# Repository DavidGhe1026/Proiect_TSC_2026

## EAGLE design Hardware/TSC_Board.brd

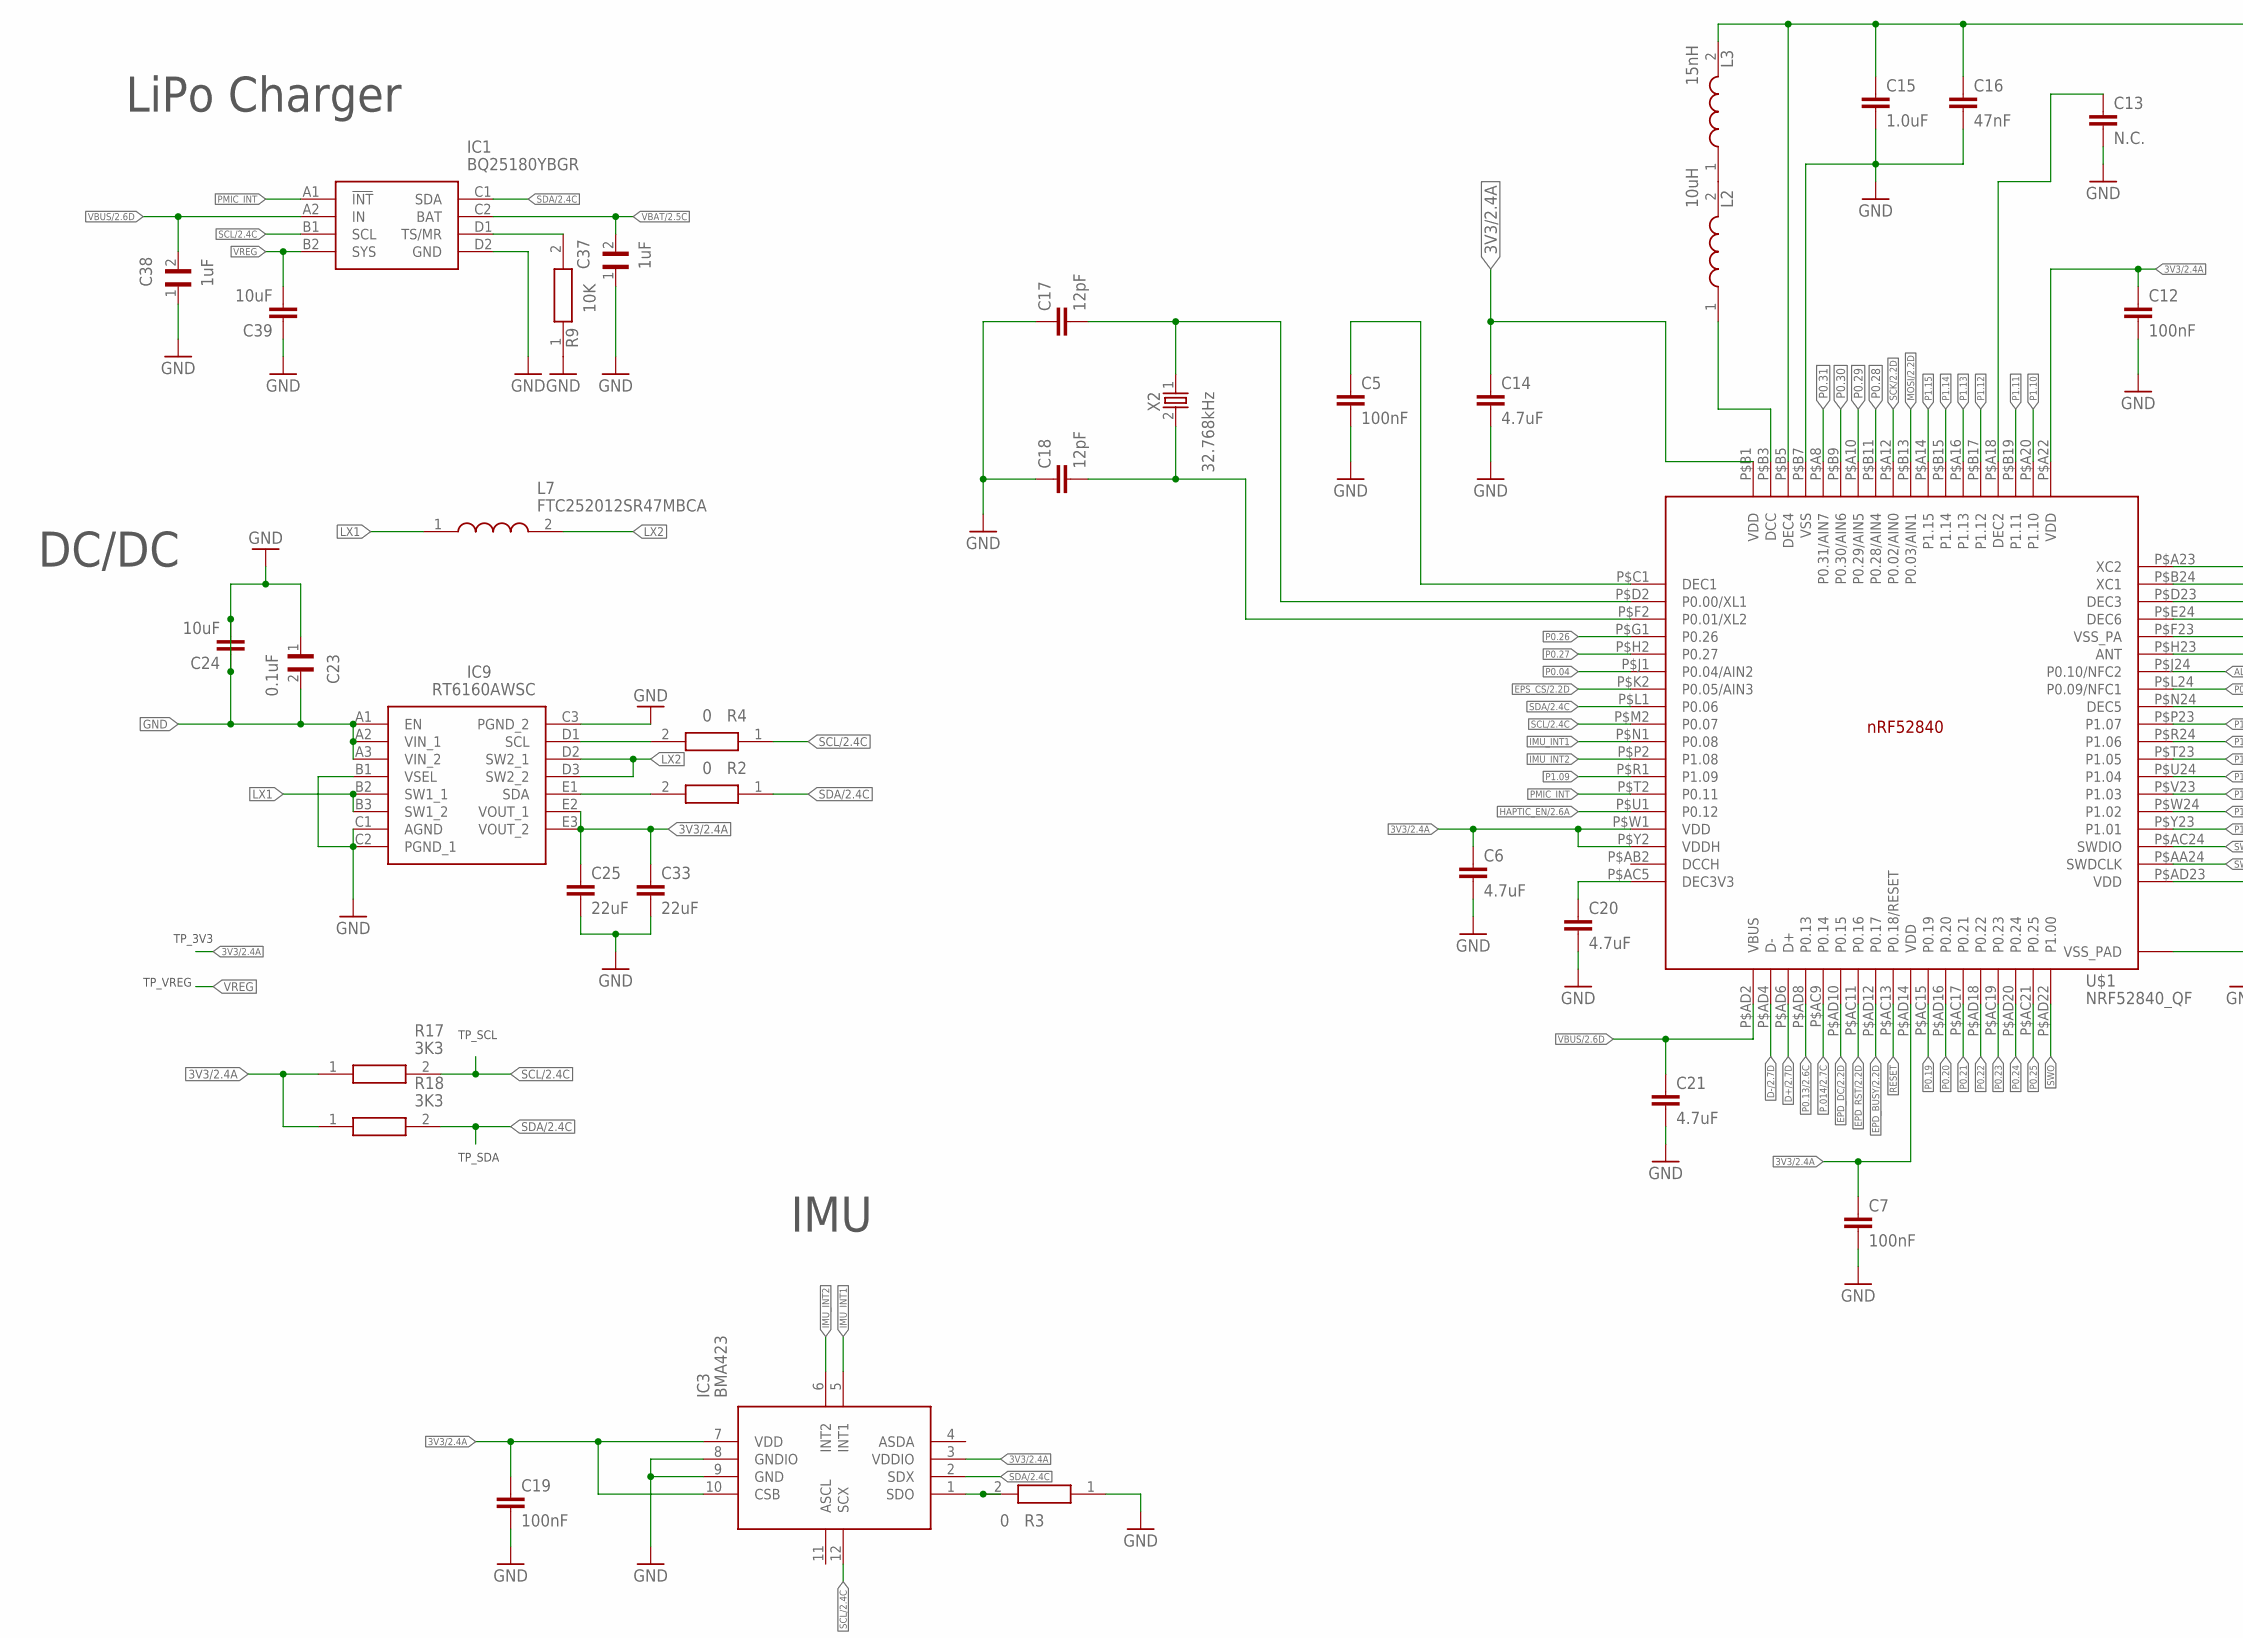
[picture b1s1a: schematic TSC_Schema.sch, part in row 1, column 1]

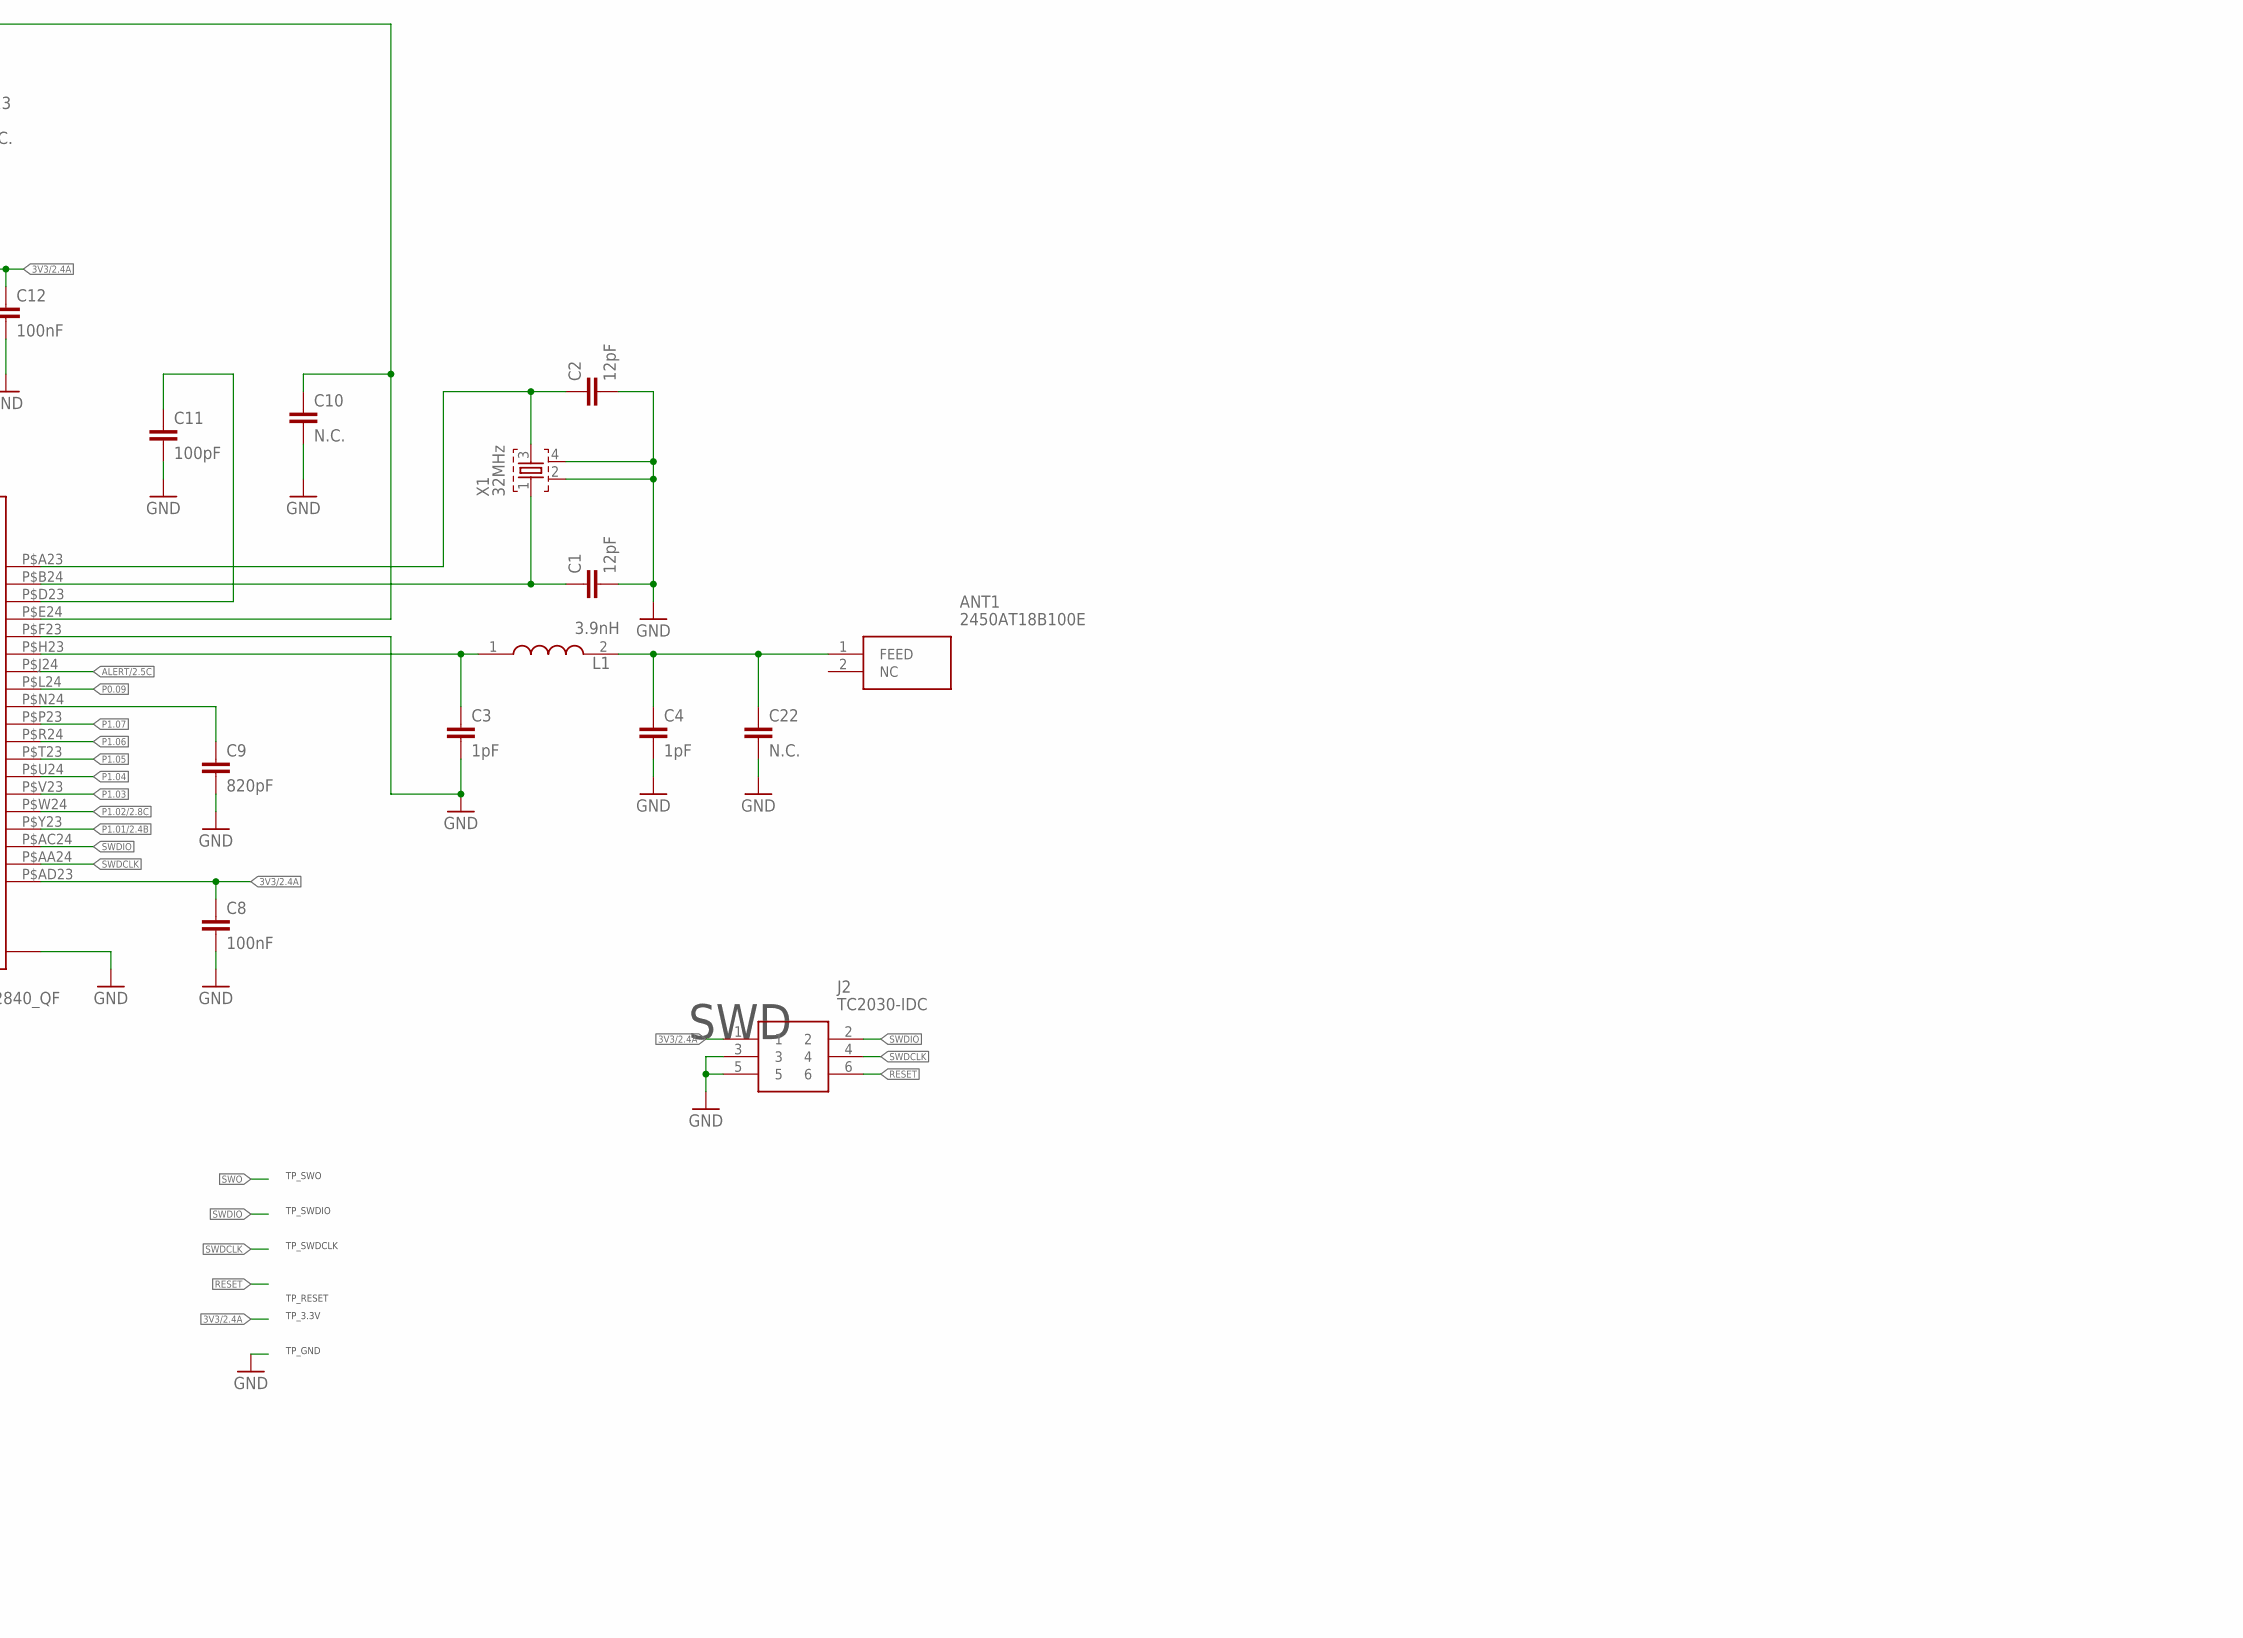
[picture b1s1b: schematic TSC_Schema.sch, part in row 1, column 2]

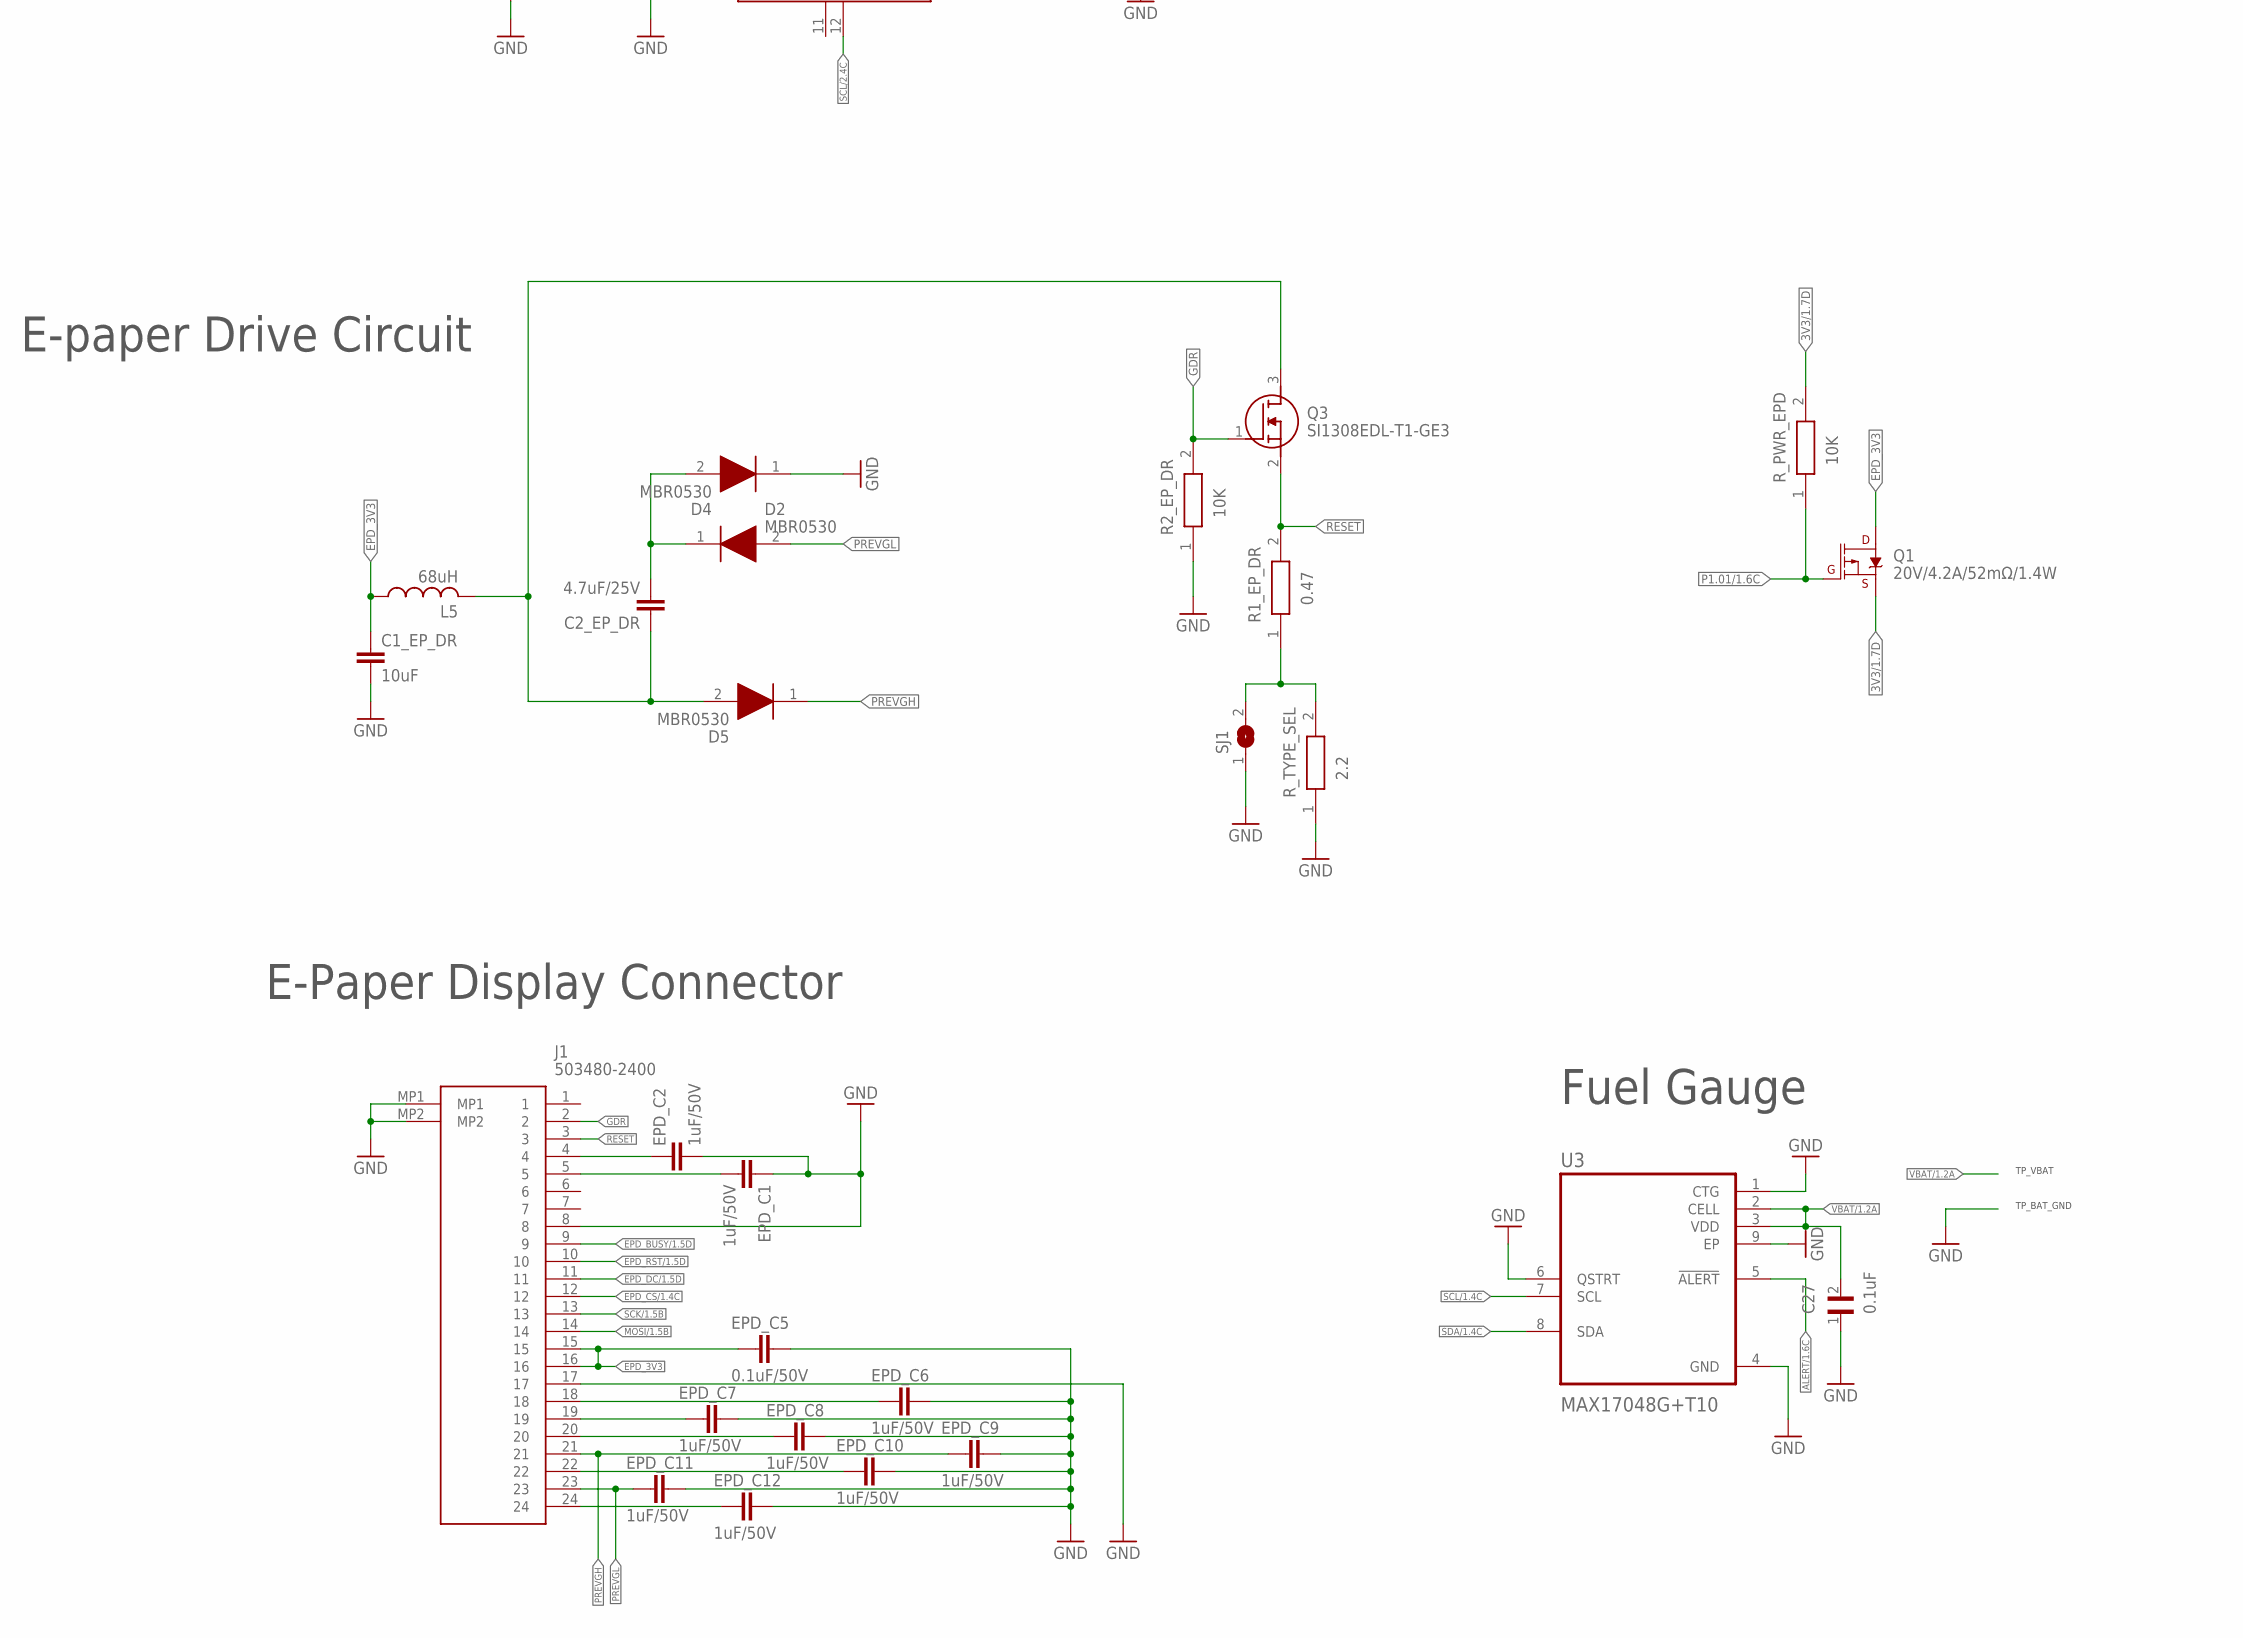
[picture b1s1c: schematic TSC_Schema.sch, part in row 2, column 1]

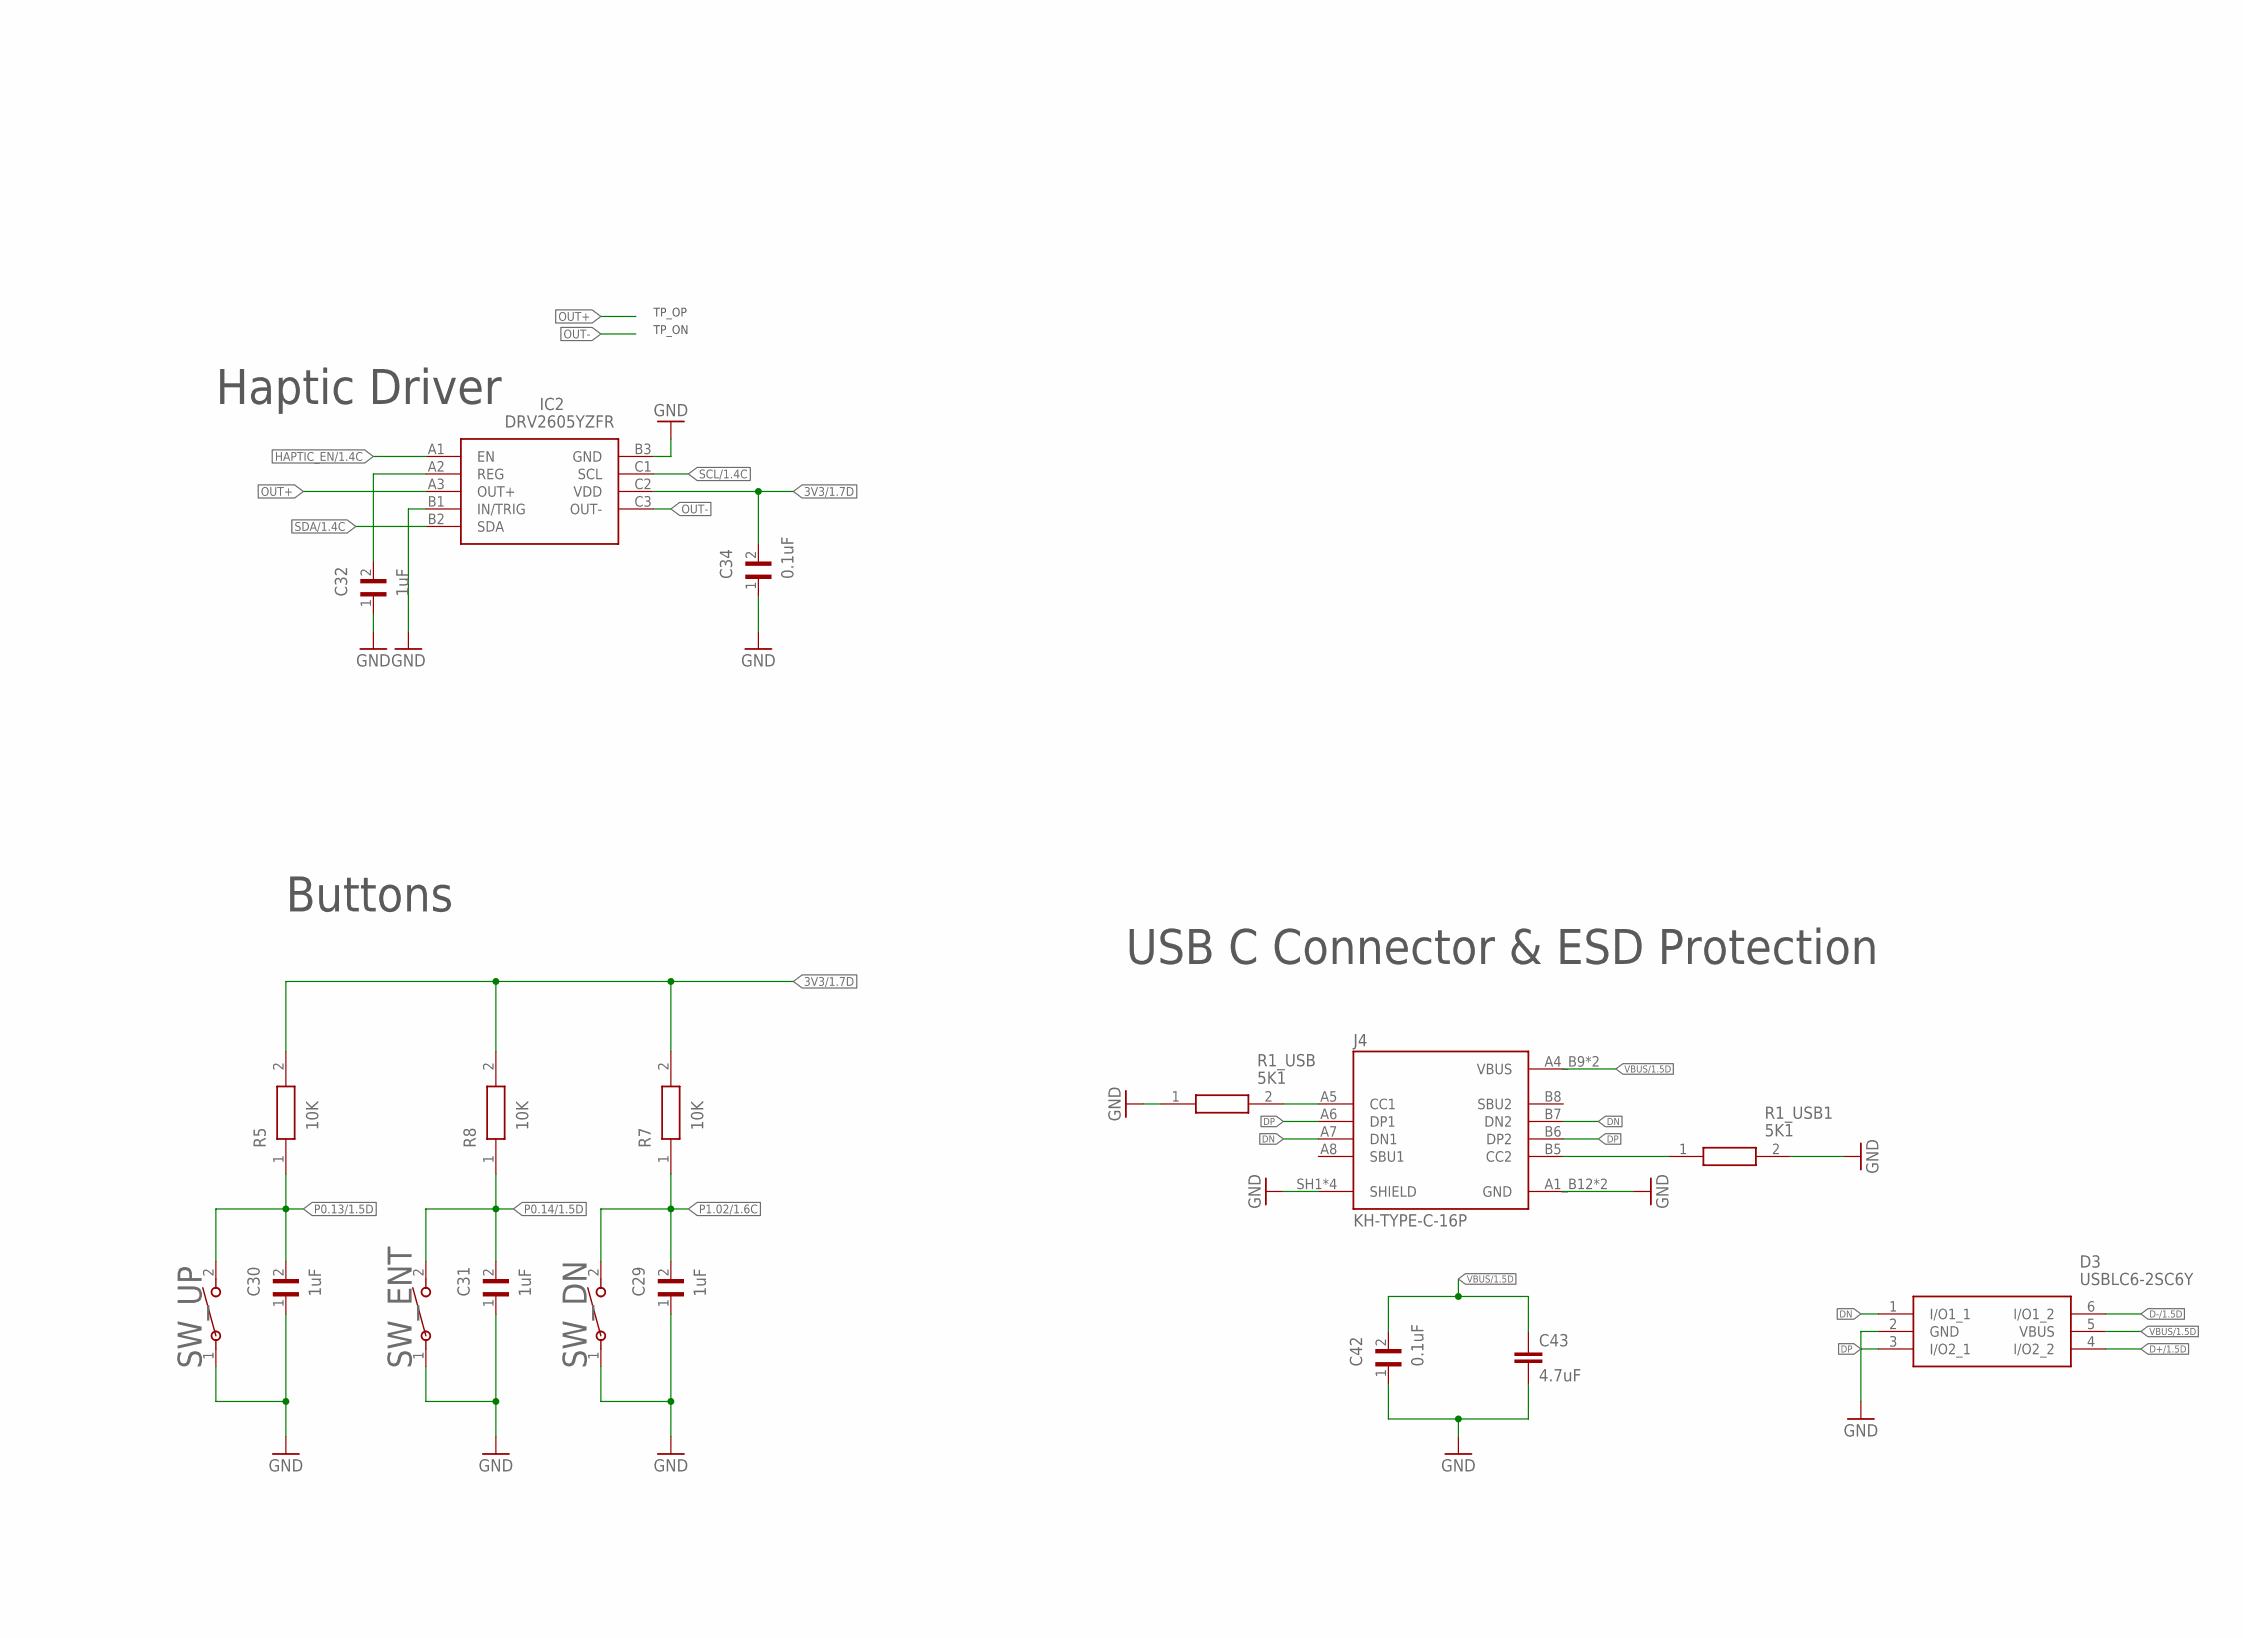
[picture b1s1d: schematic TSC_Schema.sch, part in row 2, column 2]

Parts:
ANT1: 2450AT18B100E; 2450AT18B100E_ANTC3216X140N
C1, C2, C17, C18: 12pF; NORDIC_NRF_3_RESC0402_N
C1_EP_DR, C24, C39: 10uF; NORDIC_NRF_3_RESC0402_N
C2_EP_DR: 4.7uF/25V; NORDIC_NRF_3_RESC0402_N
C3, C4: 1pF; NORDIC_NRF_3_RESC0402_N
C5, C7, C8, C12, C19: 100nF; NORDIC_NRF_3_RESC0402_N
C6, C14, C20, C21, C43: 4.7uF; NORDIC_NRF_3_RESC0402_N
C9: 820pF; NORDIC_NRF_3_RESC0402_N
C10, C13, C22: N.C.; NORDIC_NRF_3_RESC0402_N
C11: 100pF; NORDIC_NRF_3_RESC0402_N
C15: 1.0uF; ESP32_C6_LIBRARY_1_ESP32_WROVER_EAGLE-LTSPICE_C0402
C16: 47nF; ESP32_C6_LIBRARY_1_ESP32_WROVER_EAGLE-LTSPICE_C0402
C23, C27, C34, C42: 0.1uF; GRM011R60J152KE01L_2_CAPC0201X13N
C25, C33: 22uF; NORDIC_NRF_3_RESC0402_N
C29, C30, C31, C32, C37, C38: 1uF; GRM011R60J152KE01L_2_CAPC0201X13N
D2, D4, D5: MBR0530; ESP32_C6_LIBRARY_5_SOD3716X135N
D3: USBLC6-2SC6Y; ESP32_C6_LIBRARY_3_SOT95P280X145-6N
EPD_C1, EPD_C2, EPD_C6, EPD_C7, EPD_C8, EPD_C9, EPD_C10, EPD_C11, EPD_C12: 1uF/50V; NORDIC_NRF_3_RESC0402_N
EPD_C5: 0.1uF/50V; NORDIC_NRF_3_RESC0402_N
IC1: BQ25180YBGR; BQ25180YBGR_BGA8C40P2X4_100X155X50
IC2: DRV2605YZFR; DRV2605YZFR_BGA9C50P3X3_144X144X62
IC3: BMA423; BMA423_BMA423
IC9: RT6160AWSC; RT6160AWSC_BGA15C40P3X5_140X230X60
J1: 503480-2400; 503480-2400_5034802400
J2: TC2030-IDC; TC2030-IDC_TC2030IDC
J4: KH-TYPE-C-16P; KH-TYPE-C-16P_KINGHELM_KH-TYPE-C-16P
L1: 3.9nH; MLP2016SR47MT0S1_INDC2016X100N
L2: 10uH; MLP2016SR47MT0S1_INDC2016X100N
L3: 15nH; MLP2016SR47MT0S1_INDC2016X100N
L5: 68uH; NORDIC_NRF_2_RESC0402_L
L7: FTC252012SR47MBCA; MLP2016SR47MT0S1_INDC2016X100N
Q1: 20V/4.2A/52mΩ/1.4W; ESP32_C6_LIBRARY_4_ESP32_C6_LIBRARY_4_ESP32_C6_LIBRARY_4_ES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
Q3: SI1308EDL-T1-GE3; ESP32_C6_LIBRARY_6_SOT65P210X110-3N
R1_EP_DR: 0.47; CPF0201D7K68C1_0201
R1_USB, R1_USB1: 5K1; CPF0201D7K68C1_0201
R2, R3, R4: 0; CPF0201D7K68C1_0201
R2_EP_DR, R5, R7, R8, R9: 10K; CPF0201D7K68C1_0201
R17, R18: 3K3; CPF0201D7K68C1_0201
R_PWR_EPD: 10K; CPF0201D7K68C1_0201
R_TYPE_SEL: 2.2; CPF0201D7K68C1_0201
SJ1: ESP32_C6_LIBRARY_7_JUMPER_SJ
SW_DN: 2025-10-22_07-23-44_LIBRARY_EVP-AKE31ASW_EVP-AKE3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; 2025-10-22_07-23-44_LIBRARY_SW_EVP-AKE31A_PAN
SW_ENT: 2025-10-22_07-23-44_LIBRARY_EVP-AKE31ASW_EVP-AKE3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; 2025-10-22_07-23-44_LIBRARY_SW_EVP-AKE31A_PAN
SW_UP: 2025-10-22_07-23-44_LIBRARY_EVP-AKE31ASW_EVP-AKE3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; 2025-10-22_07-23-44_LIBRARY_SW_EVP-AKE31A_PAN
U3: MAX17048G+T10; ESP32_C6_LIBRARY_SON50P200X200X80-9N
U$1: NRF52840_QF; NORDIC_NRF_4_AQFN50P700X700X85_HS-74N
X1: 32MHz; NORDIC_NRF_BT-XTAL_2016_N
X2: 32.768kHz; NORDIC_NRF_1_XTAL_3215_N

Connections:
3V3/1.7D: C34.2, IC2.C2 (VDD), Q1.2 (S), R5.2, R7.2, R8.2, R_PWR_EPD.2
3V3/2.4A: C6.1, C7.1, C8.1, C12.1, C14.1, C19.1, C25.1, C33.1, IC3.3 (VDDIO), IC3.7 (VDD), IC3.10 (CSB), IC9.E2 (VOUT_1), IC9.E3 (VOUT_2), J2.1, R17.1, R18.1, U$1.P$A22 (VDD), U$1.P$AD14 (VDD), U$1.P$AD23 (VDD), U$1.P$B1 (VDD), U$1.P$W1 (VDD), U$1.P$Y2 (VDDH)
ALERT/1.6C: U3.5 (!ALERT)
ALERT/2.5C: U$1.P$J24 (P0.10/NFC2)
D+/1.5D: D3.4 (I/O2_2)
D+/2.7D: U$1.P$AD6 (D+)
D-/1.5D: D3.6 (I/O1_2)
D-/2.7D: U$1.P$AD4 (D-)
DEC3: C11.1, U$1.P$D23 (DEC3)
DEC4_6: C10.1, C15.1, C16.1, L3.2, U$1.P$B5 (DEC4), U$1.P$E24 (DEC6)
DN: D3.1 (I/O1_1), J4.A7 (DN1), J4.B7 (DN2)
DP: D3.3 (I/O2_1), J4.A6 (DP1), J4.B6 (DP2)
EPD_3V3: C1_EP_DR.1, EPD_C5.2, J1.15, J1.16, L5.1, Q1.3 (D)
EPD_BUSY/1.5D: J1.9
EPD_BUSY/2.2D: U$1.P$AD12 (P0.17)
EPD_CS/1.4C: J1.12
EPD_DC/1.5D: J1.11
EPD_DC/2.2D: U$1.P$AD10 (P0.15)
EPD_RST/1.5D: J1.10
EPD_RST/2.2D: U$1.P$AC11 (P0.16)
EPS_CS/2.2D: U$1.P$K2 (P0.05/AIN3)
GDR: J1.2, Q3.1 (G), R2_EP_DR.2
GND: C1.2, C1_EP_DR.2, C2.2, C3.2, C4.2, C5.2, C6.2, C7.2, C8.2, C9.2, C10.2, C11.2, C12.2, C13.2, C14.2, C15.2, C16.2, C17.1, C18.1, C19.2, C20.2, C21.2, C22.2, C23.1, C23.2, C24.1, C24.2, C25.2, C27.1, C29.1, C30.1, C31.1, C32.1, C33.2, C34.1, C37.1, C38.1, C39.1, C42.1, C43.2, D3.2 (GND), D4.1 (K), EPD_C1.1, EPD_C2.2, EPD_C5.1, EPD_C6.1, EPD_C7.1, EPD_C8.1, EPD_C9.1, EPD_C10.1, EPD_C11.1, EPD_C12.1, IC1.D2 (GND), IC2.B1 (IN/TRIG), IC2.B3 (GND), IC3.8 (GNDIO), IC3.9 (GND), IC9.A1 (EN), IC9.A2 (VIN_1), IC9.A3 (VIN_2), IC9.B1 (VSEL), IC9.C1 (AGND), IC9.C2 (PGND_1), IC9.C3 (PGND_2), J1.8, J1.17, J1.MP1, J1.MP2, J2.3, J2.5, J4.A1_B12 (GND), J4.A12_B1 (GND), J4.SH1 (SHIELD), J4.SH2 (SHIELD), J4.SH3 (SHIELD), J4.SH4 (SHIELD), R1_USB.1, R1_USB1.2, R2_EP_DR.1, R3.1, R9.1, R_TYPE_SEL.1, SJ1.1, SW_DN.1, SW_ENT.1, SW_UP.1, U3.1 (CTG), U3.4 (GND), U3.6 (QSTRT), U3.9 (EP), U$1.P$74 (VSS_PAD), U$1.P$75 (VSS_PAD), U$1.P$76 (VSS_PAD), U$1.P$77 (VSS_PAD), U$1.P$78 (VSS_PAD), U$1.P$79 (VSS_PAD), U$1.P$80 (VSS_PAD), U$1.P$81 (VSS_PAD), U$1.P$82 (VSS_PAD), U$1.P$83 (VSS_PAD), U$1.P$84 (VSS_PAD), U$1.P$85 (VSS_PAD), U$1.P$86 (VSS_PAD), U$1.P$87 (VSS_PAD), U$1.P$88 (VSS_PAD), U$1.P$89 (VSS_PAD), U$1.P$90 (VSS_PAD), U$1.P$B7 (VSS), U$1.P$F23 (VSS_PA), X1.2, X1.4
HAPTIC_EN/1.4C: IC2.A1 (EN)
HAPTIC_EN/2.6A: U$1.P$U1 (P0.12)
IMU_INT1: IC3.5 (INT1), U$1.P$N1 (P0.08)
IMU_INT2: IC3.6 (INT2), U$1.P$P2 (P1.08)
LX1: IC9.B2 (SW1_1), IC9.B3 (SW1_2), L7.1
LX2: IC9.D2 (SW2_1), IC9.D3 (SW2_2), L7.2
MOSI/1.5B: J1.14
MOSI/2.2D: U$1.P$B13 (P0.03/AIN1)
unnamed: L2.1, U$1.P$B3 (DCC)
unnamed: L2.2, L3.1
unnamed: C13.1, U$1.P$A18 (DEC2)
unnamed: C1.1, U$1.P$B24 (XC1), X1.1
unnamed: C2.1, U$1.P$A23 (XC2), X1.3
unnamed: ANT1.1 (FEED), C4.1, C22.1, L1.2
unnamed: C3.1, L1.1, U$1.P$H23 (ANT)
unnamed: C9.1, U$1.P$N24 (DEC5)
unnamed: C5.1, U$1.P$C1 (DEC1)
unnamed: C17.2, U$1.P$D2 (P0.00/XL1), X2.1
unnamed: C18.2, U$1.P$F2 (P0.01/XL2), X2.2
unnamed: C20.1, U$1.P$AC5 (DEC3V3)
unnamed: IC3.1 (SDO), R3.2
unnamed: IC9.D1 (SCL), R4.2
unnamed: IC9.E1 (SDA), R2.2
unnamed: IC1.D1 (TS/MR), R9.2
unnamed: C2_EP_DR.1, D5.2 (A), L5.2, Q3.3 (D)
unnamed: R1_EP_DR.1, R_TYPE_SEL.2, SJ1.2
unnamed: C2_EP_DR.2, D2.1 (K), D4.2 (A)
unnamed: C32.2, IC2.A2 (REG)
unnamed: EPD_C2.1, J1.4
unnamed: EPD_C1.2, J1.5
unnamed: EPD_C7.2, J1.19
unnamed: EPD_C6.2, J1.18
unnamed: EPD_C8.2, J1.20
unnamed: C29.2, R7.1, SW_DN.2
unnamed: EPD_C10.2, J1.22
unnamed: J4.A5 (CC1), R1_USB.2
unnamed: EPD_C12.2, J1.24
unnamed: J4.B5 (CC2), R1_USB1.1
OUT+: IC2.A3 (OUT+)
OUT-: IC2.C3 (OUT-)
P0.1: U$1.P$A10 (P0.29/AIN5)
P0.2: U$1.P$B11 (P0.28/AIN4)
P0.04: U$1.P$J1 (P0.04/AIN2)
P0.09: U$1.P$L24 (P0.09/NFC1)
P0.13/1.5D: C30.2, R5.1, SW_UP.2
P0.13/2.6C: U$1.P$AD8 (P0.13)
P0.14/1.5D: C31.2, R8.1, SW_ENT.2
P0.19: U$1.P$AC15 (P0.19)
P0.20: U$1.P$AD16 (P0.20)
P0.21: U$1.P$AC17 (P0.21)
P0.22: U$1.P$AD18 (P0.22)
P0.23: U$1.P$AC19 (P0.23)
P0.24: U$1.P$AD20 (P0.24)
P0.25: U$1.P$AC21 (P0.25)
P0.26: U$1.P$G1 (P0.26)
P0.27: U$1.P$H2 (P0.27)
P0.30: U$1.P$B9 (P0.30/AIN6)
P0.31: U$1.P$A8 (P0.31/AIN7)
P1.01/1.6C: Q1.1 (G), R_PWR_EPD.1
P1.01/2.4B: U$1.P$Y23 (P1.01)
P1.02/2.8C: U$1.P$W24 (P1.02)
P1.03: U$1.P$V23 (P1.03)
P1.04: U$1.P$U24 (P1.04)
P1.05: U$1.P$T23 (P1.05)
P1.06: U$1.P$R24 (P1.06)
P1.07: U$1.P$P23 (P1.07)
P1.09: U$1.P$R1 (P1.09)
P1.10: U$1.P$A20 (P1.10)
P1.11: U$1.P$B19 (P1.11)
P1.12: U$1.P$B17 (P1.12)
P1.13: U$1.P$A16 (P1.13)
P1.14: U$1.P$B15 (P1.14)
P1.15: U$1.P$A14 (P1.15)
P.014/2.7C: U$1.P$AC9 (P0.14)
PMIC_INT: IC1.A1 (!INT), U$1.P$T2 (P0.11)
PREVGH: D5.1 (K), EPD_C9.2, J1.21
PREVGL: D2.2 (A), EPD_C11.2, J1.23
RESET: J1.3, J2.6, Q3.2 (S), R1_EP_DR.2, U$1.P$AC13 (P0.18/RESET)
SCK/1.5B: J1.13
SCK/2.2D: U$1.P$A12 (P0.02/AIN0)
SCL/1.4C: IC2.C1 (SCL), U3.7 (SCL)
SCL/2.4C: IC1.B1 (SCL), IC3.12 (SCX), R4.1, R17.2, U$1.P$M2 (P0.07)
SDA/1.4C: IC2.B2 (SDA), U3.8 (SDA)
SDA/2.4C: IC1.C1 (SDA), IC3.2 (SDX), R2.1, R18.2, U$1.P$L1 (P0.06)
SWDCLK: J2.4, U$1.P$AA24 (SWDCLK)
SWDIO: J2.2, U$1.P$AC24 (SWDIO)
SWO: U$1.P$AD22 (P1.00)
VBAT/1.2A: C27.2, U3.2 (CELL), U3.3 (VDD)
VBAT/2.5C: C37.2, IC1.C2 (BAT)
VBUS/1.5D: C42.2, C43.1, D3.5 (VBUS), J4.A4_B9 (VBUS), J4.A9_B4 (VBUS)
VBUS/2.6D: C21.1, C38.2, IC1.A2 (IN), U$1.P$AD2 (VBUS)
VREG: C39.2, IC1.B2 (SYS)

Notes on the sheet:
SWD
TP_SWO
TP_SWDCLK
TP_SWDIO
TP_RESET
TP_3.3V
TP_GND
IMU
TP_SCL
TP_SDA
TP_3V3
TP_VREG
DC/DC
LiPo Charger
E-paper Drive Circuit
TP_OP
TP_ON
Haptic Driver
E-Paper Display Connector
TP_VBAT
TP_BAT_GND
Fuel Gauge
Buttons
USB C Connector & ESD Protection

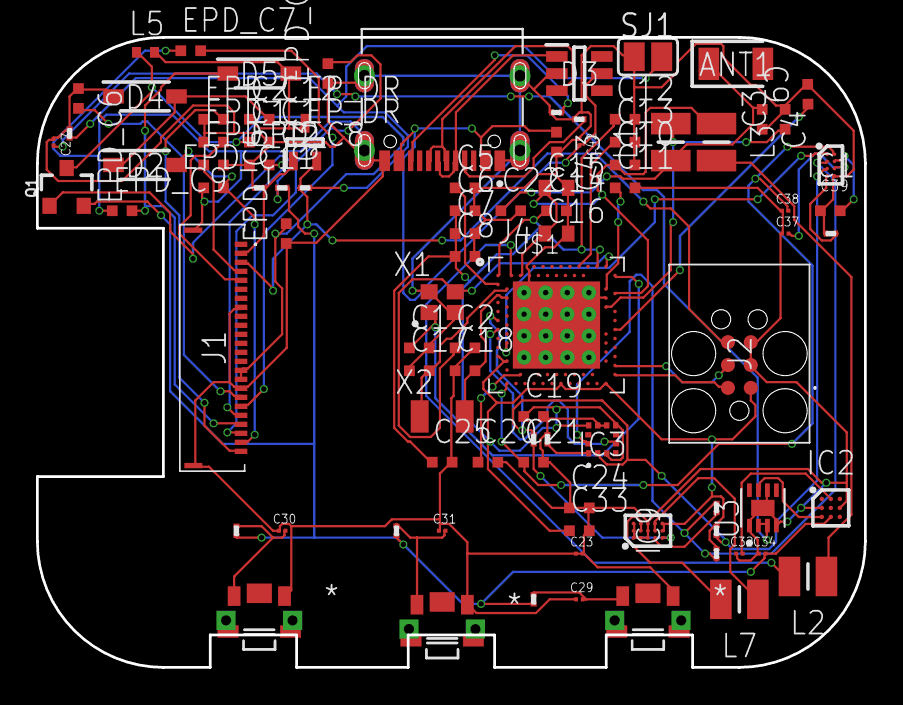
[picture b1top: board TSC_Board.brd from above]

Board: 4 copper layers, 46.0 x 35.0 mm, 91 parts (0 on the bottom side), 61 nets.

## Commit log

2026-04-11 Adaugare fisier .sch
2026-04-14 Added LICENSE
2026-04-15 Added README.md
2026-04-15 Modified README.md
2026-04-15 Fixed diagram in README.md
2026-04-18 Added .brd file
2026-04-19 Added Print-out PDF

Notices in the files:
parts and their libraries:
COPYRIGHT: Copyright (C) 2025 Ultra Librarian. All rights reserved.
